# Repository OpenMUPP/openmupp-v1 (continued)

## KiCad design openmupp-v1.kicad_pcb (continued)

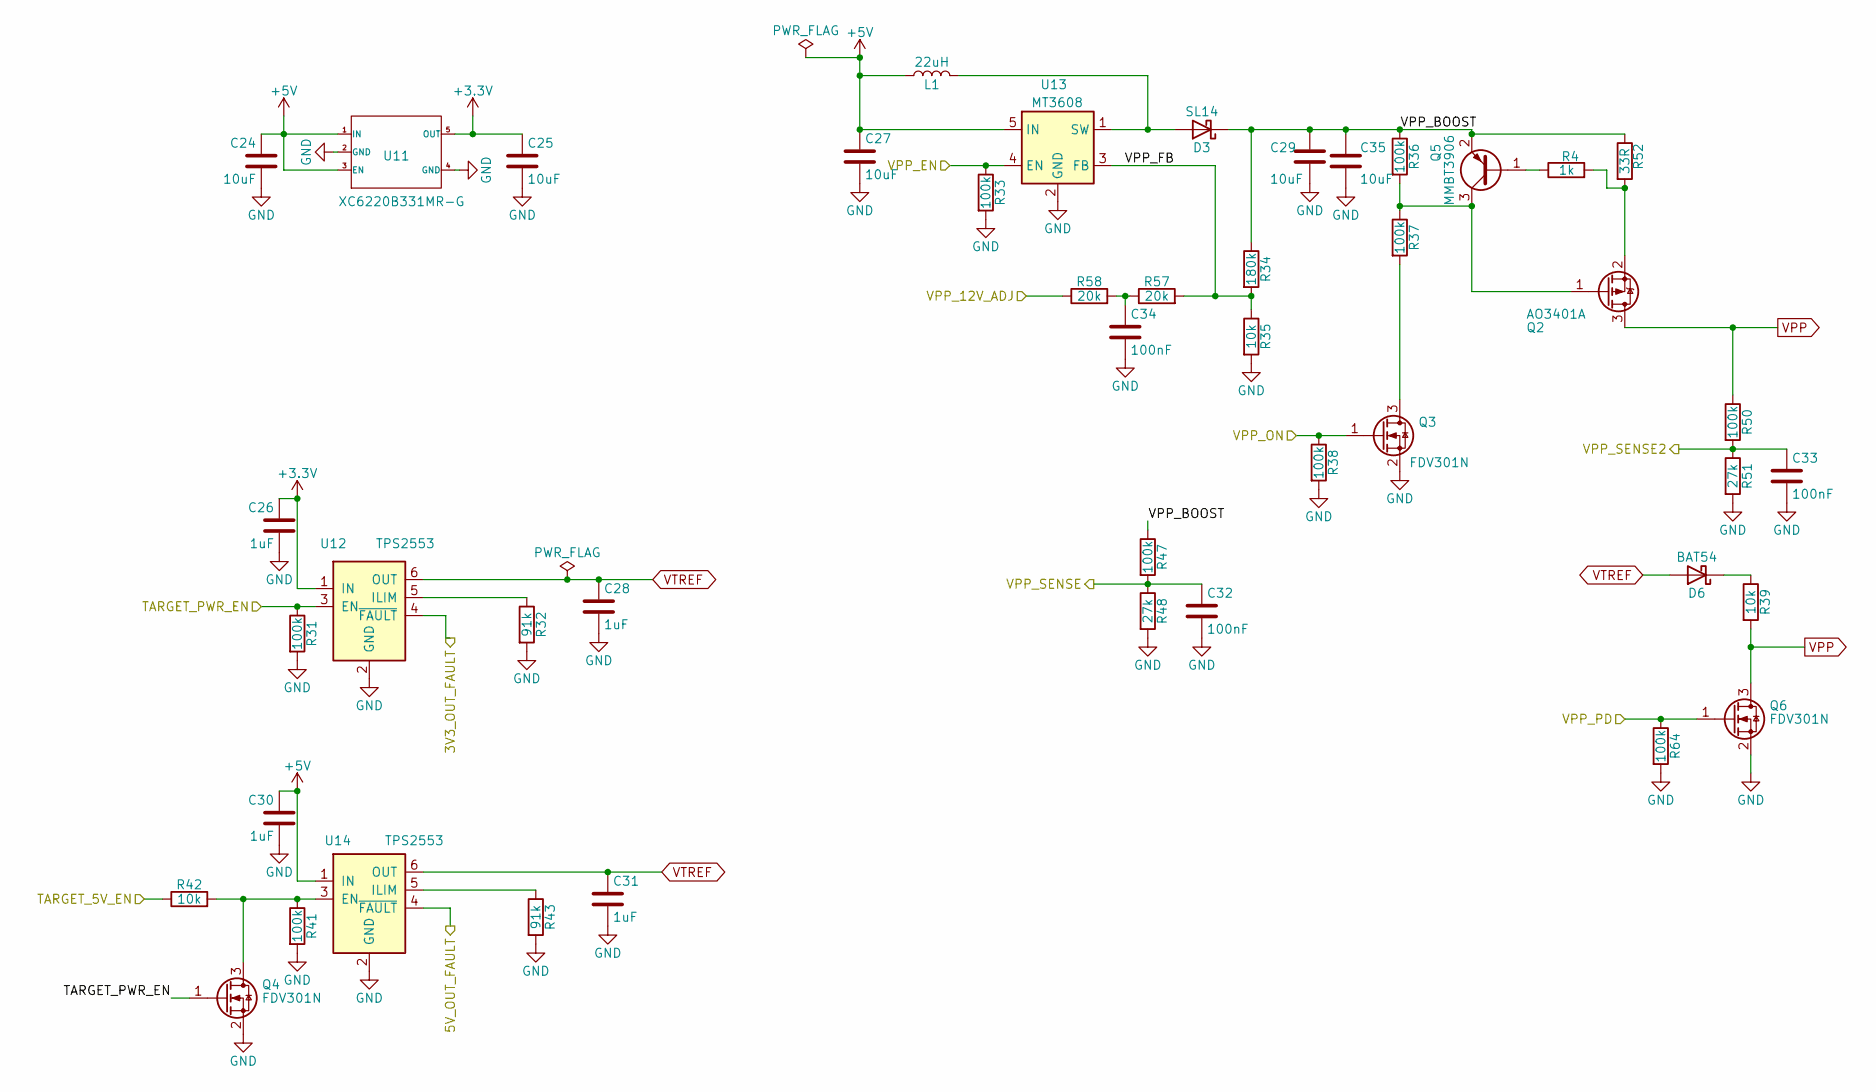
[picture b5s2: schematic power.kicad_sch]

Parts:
C24, C25: 10uF; C_1206; LCSC C13585
C26, C28, C30, C31: 1uF; C_0603; LCSC C15849
C27, C29, C35: 10uF; C_0805; LCSC C15850
C32, C33, C34: 100nF; C_0603; LCSC C14663
D3: SL14; D_SOD-123; LCSC C698818
D6: BAT54; D_SOD-323; LCSC C21107
L1: 22uH; L_FNR5040S; LCSC C167971
Q2: AO3401A; SOT-23; LCSC C15127
Q3, Q4, Q6: FDV301N; SOT-23; LCSC C15310
Q5: MMBT3906; SOT-23; LCSC C2940
R4: 1k; R_0402; LCSC C11702
R31, R33, R36, R37, R38, R41, R47, R50, R64: 100k; R_0402; LCSC C25741
R32, R43: 91k; R_0603; LCSC C23265
R34: 180k; R_0402; LCSC C25760
R35, R39, R42: 10k; R_0402; LCSC C25744
R48, R51: 27k; R_0402; LCSC C25771
R52: 33R; R_0402; LCSC C25105
R57, R58: 20k; R_0402; LCSC C25765
U11: XC6220B331MR-G; SOT23_5L; LCSC C3040644
U12, U14: TPS2553; SOT-23-6; LCSC C111738
U13: MT3608; SOT23_6L; LCSC C84817

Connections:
/3V3_OUT_FAULT: U12.4 (~FAULT); also elsewhere on the board
/5V_OUT_FAULT: U14.4 (~FAULT); also elsewhere on the board
/Power/VPP_BOOST: C29.1, C35.1, D3.1 (K), Q5.2 (E), R34.1, R36.1, R47.1, R52.1
/Power/VPP_FB: R34.2, R35.1, R57.2, U13.3 (FB)
/TARGET_5V_EN: R42.1; also elsewhere on the board
/TARGET_PWR_EN: Q4.1 (G), R31.1, U12.3 (EN); also elsewhere on the board
/VPP_12V_ADJ: R58.1; also elsewhere on the board
/VPP_EN: R33.1, U13.4 (EN); also elsewhere on the board
/VPP_ON: Q3.1 (G), R38.1; also elsewhere on the board
/VPP_PD: Q6.1 (G), R64.1; also elsewhere on the board
/VPP_SENSE: C32.1, R47.2, R48.1; also elsewhere on the board
/VPP_SENSE2: C33.1, R50.2, R51.1; also elsewhere on the board
unnamed: C34.1, R57.1, R58.2
unnamed: D3.2 (A), L1.2, U13.1 (SW)
unnamed: D6.1 (K), R39.1
unnamed: Q2.1 (G), Q5.3 (C), R36.2, R37.1
unnamed: Q2.2 (S), R4.2, R52.2
unnamed: Q3.3 (D), R37.2
unnamed: Q4.3 (D), R41.1, R42.2, U14.3 (EN)
unnamed: Q5.1 (B), R4.1
unnamed: R32.1, U12.5 (ILIM)
unnamed: R43.1, U14.5 (ILIM)
VPP: Q2.3 (D), Q6.3 (D), R39.2, R50.1; also elsewhere on the board

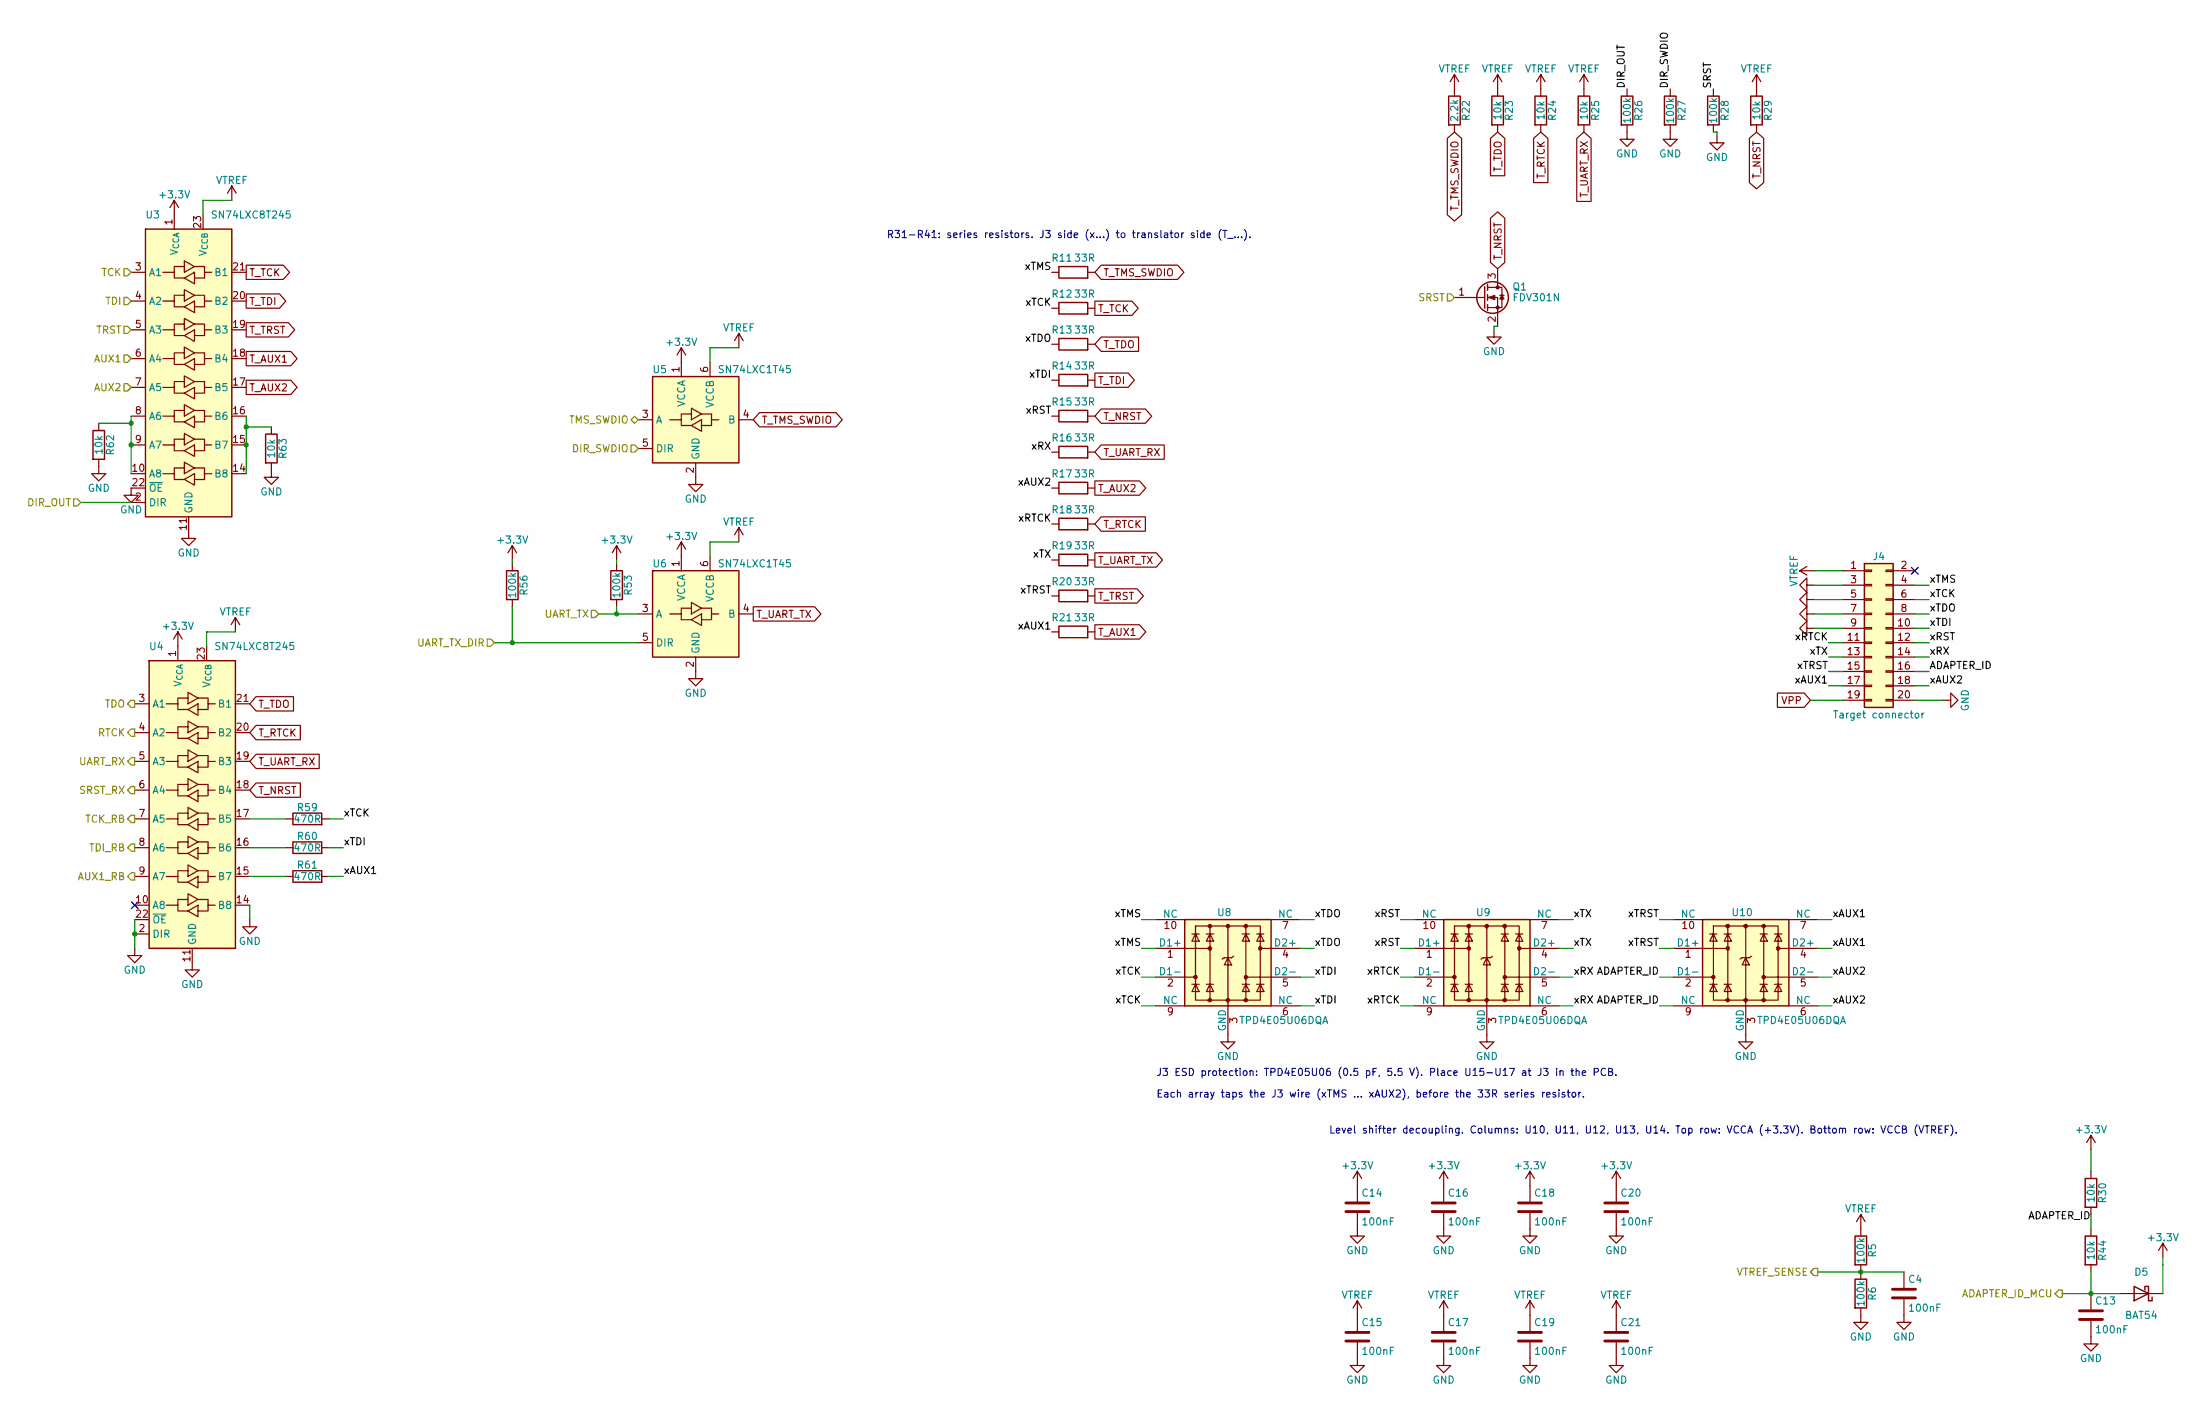
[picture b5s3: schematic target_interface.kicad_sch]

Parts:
C4, C13, C14, C15, C16, C17, C18, C19, C20, C21: 100nF; C_0603; LCSC C14663
D5: BAT54; D_SOD-323; LCSC C21107
J4: Target connector; IDC-Header_2x10_P2.54mm_Horizontal
Q1: FDV301N; SOT-23; LCSC C15310
R5, R6, R26, R27, R28, R53, R56: 100k; R_0402; LCSC C25741
R11, R12, R13, R14, R15, R16, R17, R18, R19, R20, R21: 33R; R_0402; LCSC C25105
R22: 2.2k; R_0402; LCSC C25879
R23, R24, R25, R29, R30, R44, R62, R63: 10k; R_0402; LCSC C25744
R59, R60, R61: 470R; R_0402; LCSC C25117
U3, U4: SN74LXC8T245; TSSOP-24_4.4x7.8mm_P0.65mm; LCSC C4363995
U5, U6: SN74LXC1T45; SOT-23-6; LCSC C4364198
U8, U9, U10: TPD4E05U06DQA; USON-10_2.5x1.0mm_P0.5mm; LCSC C138714

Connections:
/ADAPTER_ID_MCU: C13.1, D5.2 (A), R44.2; also elsewhere on the board
/AUX1: U3.6 (A4); also elsewhere on the board
/AUX1_RB: U4.9 (A7); also elsewhere on the board
/AUX2: U3.7 (A5); also elsewhere on the board
/DIR_OUT: R26.1, U3.2 (DIR); also elsewhere on the board
/DIR_SWDIO: R27.1, U5.5 (DIR); also elsewhere on the board
/RTCK: U4.4 (A2); also elsewhere on the board
/SRST: Q1.1 (G), R28.1; also elsewhere on the board
/SRST_RX: U4.6 (A4); also elsewhere on the board
/TCK: U3.3 (A1); also elsewhere on the board
/TCK_RB: U4.7 (A5); also elsewhere on the board
/TDI: U3.4 (A2); also elsewhere on the board
/TDI_RB: U4.8 (A6); also elsewhere on the board
/TDO: U4.3 (A1); also elsewhere on the board
/TMS_SWDIO: U5.3 (A); also elsewhere on the board
/TRST: U3.5 (A3); also elsewhere on the board
/Target interface/ADAPTER_ID: J4.16, R30.2, R44.1, U10.2 (D1-), U10.9 (NC)
/Target interface/xAUX1: J4.17, R21.1, R61.2, U10.4 (D2+), U10.7 (NC)
/Target interface/xAUX2: J4.18, R17.1, U10.5 (D2-), U10.6 (NC)
/Target interface/xRST: J4.12, R15.1, U9.1 (D1+), U9.10 (NC)
/Target interface/xRTCK: J4.11, R18.1, U9.2 (D1-), U9.9 (NC)
/Target interface/xRX: J4.14, R16.1, U9.5 (D2-), U9.6 (NC)
/Target interface/xTCK: J4.6, R12.1, R59.2, U8.2 (D1-), U8.9 (NC)
/Target interface/xTDI: J4.10, R14.1, R60.2, U8.5 (D2-), U8.6 (NC)
/Target interface/xTDO: J4.8, R13.1, U8.4 (D2+), U8.7 (NC)
/Target interface/xTMS: J4.4, R11.1, U8.1 (D1+), U8.10 (NC)
/Target interface/xTRST: J4.15, R20.1, U10.1 (D1+), U10.10 (NC)
/Target interface/xTX: J4.13, R19.1, U9.4 (D2+), U9.7 (NC)
/UART_RX: U4.5 (A3); also elsewhere on the board
/UART_TX: R53.2, U6.3 (A); also elsewhere on the board
/UART_TX_DIR: R56.2, U6.5 (DIR); also elsewhere on the board
/VTREF_SENSE: C4.1, R5.2, R6.1; also elsewhere on the board
unnamed: R62.1, U3.8 (A6), U3.9 (A7), U3.10 (A8)
unnamed: R63.1, U3.14 (B8), U3.15 (B7), U3.16 (B6)
unnamed: R59.1, U4.17 (B5)
unnamed: R60.1, U4.16 (B6)
unnamed: R61.1, U4.15 (B7)
T_AUX1: R21.2, U3.18 (B4)
T_AUX2: R17.2, U3.17 (B5)
T_NRST: Q1.3 (D), R15.2, R29.2, U4.18 (B4)
T_RTCK: R18.2, R24.2, U4.20 (B2)
T_TCK: R12.2, U3.21 (B1)
T_TDI: R14.2, U3.20 (B2)
T_TDO: R13.2, R23.2, U4.21 (B1)
T_TMS_SWDIO: R11.2, R22.2, U5.4 (B)
T_TRST: R20.2, U3.19 (B3)
T_UART_RX: R16.2, R25.2, U4.19 (B3)
T_UART_TX: R19.2, U6.4 (B)
VPP: J4.19; also elsewhere on the board

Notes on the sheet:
J3 ESD protection: TPD4E05U06 (0.5 pF, 5.5 V). Place U15-U17 at J3 in the PCB.
Each array taps the J3 wire (xTMS ... xAUX2), before the 33R series resistor.
R31-R41: series resistors. J3 side (x...) to translator side (T_...).
Level shifter decoupling. Columns: U10, U11, U12, U13, U14. Top row: VCCA (+3.3V). Bottom row: VCCB (VTREF).

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
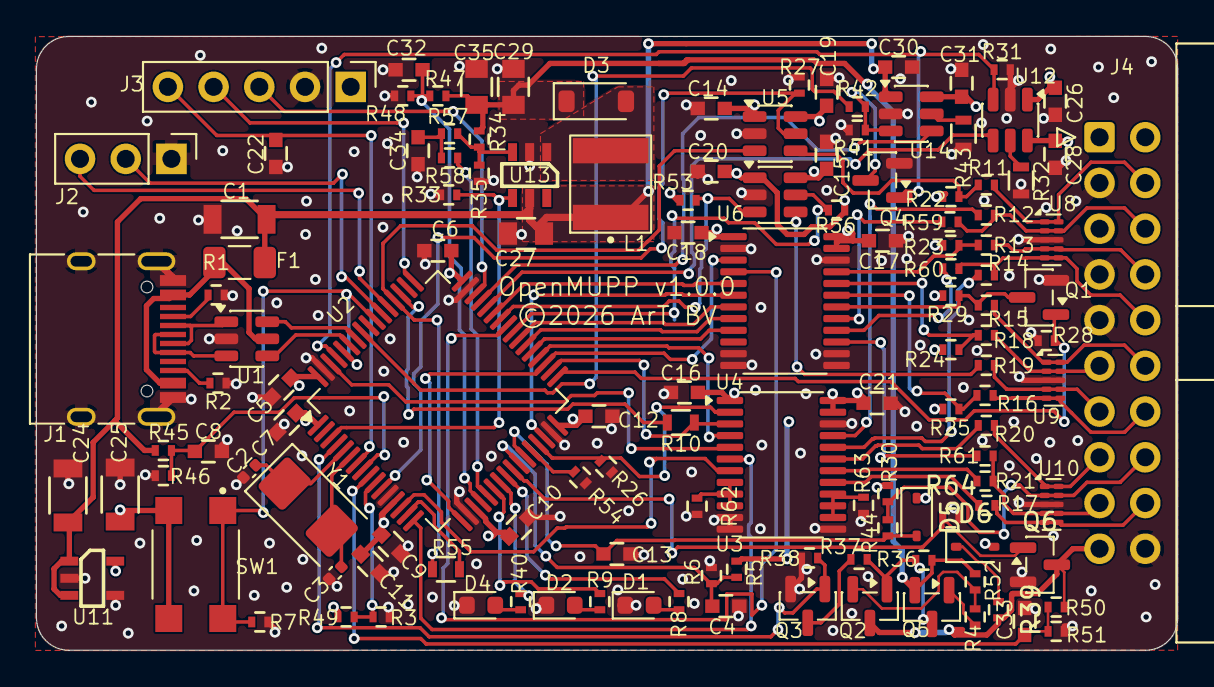
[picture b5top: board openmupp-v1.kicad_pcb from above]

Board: 4 copper layers, 63.4 x 34.1 mm, 131 parts (0 on the bottom side), 101 nets.

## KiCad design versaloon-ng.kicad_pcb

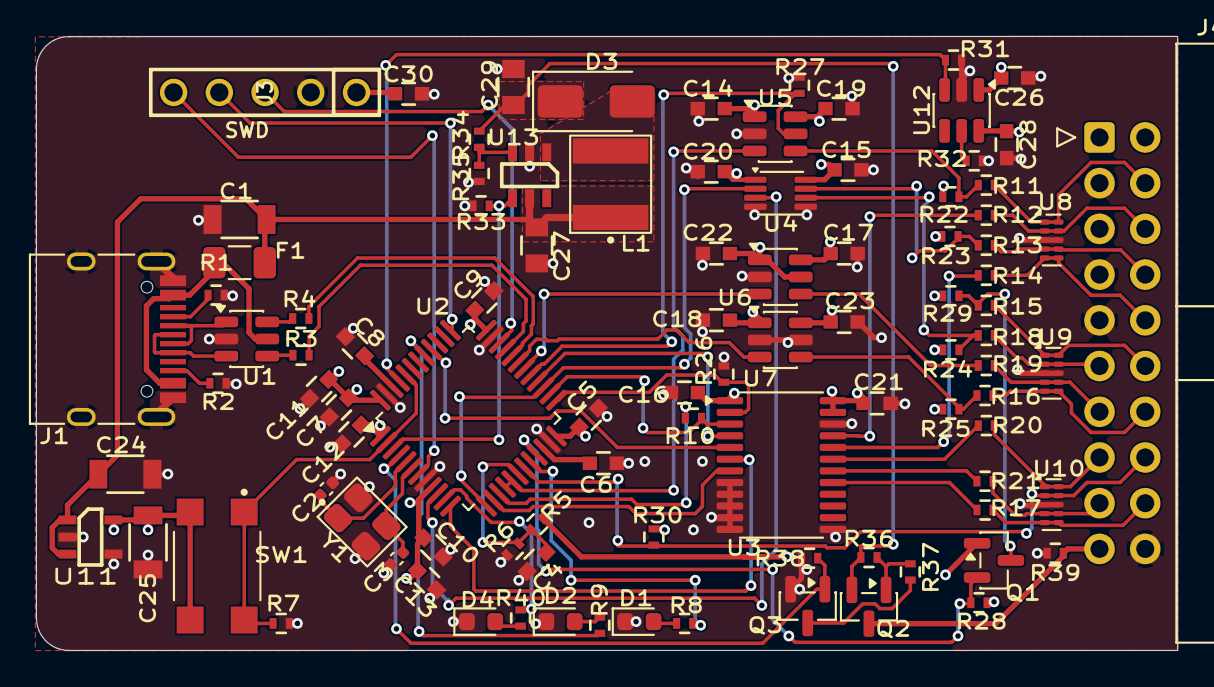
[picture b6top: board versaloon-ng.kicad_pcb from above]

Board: 4 copper layers, 63.4 x 34.1 mm, 97 parts (0 on the bottom side), 75 nets.

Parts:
C1, C24, C25: 10uF; C_1206
C2, C3: 5.6pF; C_0402_1005Metric
C4, C5, C7, C9, C10, C12, C14, C15, C16, C17, C18, C19, C20, C21, C22, C23, C30: 100nF; C_0603
C6, C8: 2.2uF; C_0603
C11: 4.7uF; C_0603
C13, C26, C28: 1uF; C_0603
C27, C29: 10uF; C_0805
D1, D4: LED state; LED_0603_1608Metric
D2: LED USB; LED_0603_1608Metric
D3: SL14; D_SMA
F1: 750mA; Fuse_1206_3216Metric
J1: USB_C_Receptacle_USB2.0_16P; USB_C_Receptacle_HRO_TYPE-C-31-M-12
J3: SWD; CON_HDR_1x5_2.54mm
J4: Target connector; IDC-Header_2x10_P2.54mm_Horizontal
L1: 22uH; L_FNR5040S
Q1, Q3: BSS138; SOT-23
Q2: AO3401A; SOT-23
R1, R2: 5K1; R_0402
R3, R4: 22R; R_0402
R5, R6, R26, R27, R31, R33, R36, R38, R39: 100k; R_0402
R7, R22, R23, R24, R25, R28, R29, R30, R35, R37: 10k; R_0402
R8, R9, R40: 1k; R_0402
R10: 0R; R_0402
R11, R12, R13, R14, R15, R16, R17, R18, R19, R20, R21: 33R; R_0402
R32: 51k; R_0402
R34: 191k; R_0402
SW1: BOOT0; SW_Push_HanElectricity_TS1109_4.5x4.5mm_H3.8mm
U1: USBLC6-2SC6; SOT-23-6
U2: STM32H523CCTx; LQFP-48_7x7mm_P0.5mm
U3: SN74LXC8T245; TSSOP-24_4.4x7.8mm_P0.65mm
U4: SN74LXC2T45; VSSOP-8_2.3x2mm_P0.5mm
U5, U6, U7: SN74LXC1T45; SOT-23-6
U8, U9, U10: TPD4E05U06DQA; USON-10_2.5x1.0mm_P0.5mm
U11: XC6220B331MR-G; SOT23_5L
U12: TPS2553; SOT-23-6
U13: MT3608; SOT23_6L
Y1: 24MHz; Crystal_SMD_NDK_NX3225GA_3.2x2.5mm

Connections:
+3.3V: C5.1, C7.1, C9.1, C10.1, C11.1, C12.1, C13.1, C14.1, C16.1, C18.1, C20.1, C22.1, C25.1, C26.1, C30.1, J3.1, Q1.1 (G), R28.1, R30.1, SW1.2, U2.1 (VBAT), U2.9 (VDDA), U2.24 (VDD), U2.36 (VDD), U2.48 (VDD), U3.1 (V_{CCA}), U4.1 (VCCA), U5.1 (VCCA), U6.1 (VCCA), U6.5 (DIR), U7.1 (VCCA), U11.5 (OUT), U12.1 (IN)
+5V: C1.1, C24.1, C27.1, F1.1, L1.1, U11.1 (IN), U11.3 (EN), U13.5 (IN)
/ADAPTER_ID: J4.16, R30.2, U2.19 (PB1), U10.2 (D1-), U10.9 (NC)
/AUX1: U2.12 (PA2), U3.6 (A4)
/AUX2: U2.14 (PA4), U3.7 (A5)
/BOOT0: R7.1, SW1.1, U2.2 (PC13), U2.44 (BOOT0)
/DIR_OUT: R26.1, U2.25 (PB12), U3.2 (DIR)
/DIR_SWDIO: R27.1, U2.29 (PA8), U5.5 (DIR)
/HSE_IN: C2.1, U2.5 (PH0), Y1.1
/HSE_OUT: C3.1, U2.6 (PH1), Y1.3
/LED_STATE1: R8.1, U2.20 (PB2)
/LED_STATE2: R40.1, U2.11 (PA1)
/LED_USB: R9.1, U2.41 (PB5)
/RTCK: U2.10 (PA0), U4.3 (A2)
/SRST: Q1.2 (S), R28.2, U2.21 (PB10)
/TARGET_PWR_EN: R31.1, U2.45 (PB8), U12.3 (EN)
/TCK: R10.2, U2.26 (PB13), U3.3 (A1)
/TDI: U2.28 (PB15), U3.4 (A2)
/TDO: U2.13 (PA3), U2.27 (PB14), U4.2 (A1)
/TMS_SWDIO: U2.16 (PA6), U2.17 (PA7), U5.3 (A)
/TRST: U2.40 (PB4(NJTRST)), U3.5 (A3)
/Target interface/xAUX1: J4.17, R21.1, U10.4 (D2+), U10.7 (NC)
/Target interface/xAUX2: J4.18, R17.1, U10.5 (D2-), U10.6 (NC)
/Target interface/xRST: J4.12, R15.1, U9.1 (D1+), U9.10 (NC)
/Target interface/xRTCK: J4.11, R18.1, U9.2 (D1-), U9.9 (NC)
/Target interface/xRX: J4.14, R16.1, U9.5 (D2-), U9.6 (NC)
/Target interface/xTCK: J4.6, R12.1, U8.2 (D1-), U8.9 (NC)
/Target interface/xTDI: J4.10, R14.1, U8.5 (D2-), U8.6 (NC)
/Target interface/xTDO: J4.8, R13.1, U8.4 (D2+), U8.7 (NC)
/Target interface/xTMS: J4.4, R11.1, U8.1 (D1+), U8.10 (NC)
/Target interface/xTRST: J4.15, R20.1, U10.1 (D1+), U10.10 (NC)
/Target interface/xTX: J4.13, R19.1, U9.4 (D2+), U9.7 (NC)
/UART_RX: U2.31 (PA10), U7.3 (A)
/UART_TX: U2.30 (PA9), U6.3 (A)
/VPP_EN: R33.1, U2.3 (PC14), U13.4 (EN)
/VPP_ON: Q3.1 (G), R38.1, U2.4 (PC15)
/VTREF_SENSE: C4.1, R5.2, R6.1, U2.18 (PB0)
GND: C1.2, C2.2, C3.2, C4.2, C5.2, C6.2, C7.2, C8.2, C9.2, C10.2, C11.2, C12.2, C13.2, C14.2, C15.2, C16.2, C17.2, C18.2, C19.2, C20.2, C21.2, C22.2, C23.2, C24.2, C25.2, C26.2, C27.2, C28.2, C29.2, C30.2, D1.1 (K), D2.1 (K), D4.1 (K), J1.A1 (GND), J1.A12 (GND), J1.B1 (GND), J1.B12 (GND), J1.S1 (SHIELD), J3.2, J4.3, J4.5, J4.7, J4.9, J4.20, Q3.2 (S), R1.2, R2.1, R6.2, R7.2, R26.2, R27.2, R31.2, R32.2, R33.2, R35.2, R38.2, R39.2, U1.2 (GND), U2.8 (VSSA), U2.23 (VSS), U2.35 (VSS), U2.47 (VSS), U3.8 (A6), U3.9 (A7), U3.10 (A8), U3.11 (GND), U3.12 (GND), U3.13 (GND), U3.22 (~OE), U4.4 (GND), U4.5 (DIR), U5.2 (GND), U6.2 (GND), U7.2 (GND), U7.5 (DIR), U8.3 (GND), U8.8 (GND), U9.3 (GND), U9.8 (GND), U10.3 (GND), U10.8 (GND), U11.2 (GND), U11.4 (GND), U12.2 (GND), U13.2 (GND), Y1.2 (G), Y1.4 (G)
unnamed: C6.1, U2.22 (VCAP)
unnamed: C8.1, U2.46 (VCAP)
unnamed: D1.2 (A), R8.2
unnamed: D2.2 (A), R9.2
unnamed: D3.2 (A), L1.2, U13.1 (SW)
unnamed: C29.1, D3.1 (K), Q2.2 (S), R34.1, R36.1
unnamed: D4.2 (A), R40.2
unnamed: J1.A5 (CC1), R1.1
unnamed: J1.B5 (CC2), R2.2
unnamed: J1.A6 (D+), J1.B6 (D+), U1.3 (I/O2)
unnamed: J1.A7 (D-), J1.B7 (D-), U1.1 (I/O1)
unnamed: Q2.1 (G), R36.2, R37.1
unnamed: Q3.3 (D), R37.2
unnamed: R3.1, U1.4 (I/O2)
unnamed: R4.1, U1.6 (I/O1)
unnamed: R10.1, U2.15 (PA5)
unnamed: R32.1, U12.5 (ILIM)
unnamed: R34.2, R35.1, U13.3 (FB)
RESET: J3.5, U2.7 (NRST)
SWDCLK: J3.4, U2.37 (PA14(JTCK)
SWDIO: J3.3, U2.34 (PA13(JTMS)
T_AUX1: R21.2, U3.18 (B4)
T_AUX2: R17.2, U3.17 (B5)
T_NRST: Q1.3 (D), R15.2, R29.2
T_RTCK: R18.2, R24.2, U4.6 (B2)
T_TCK: R12.2, U3.21 (B1)
T_TDI: R14.2, U3.20 (B2)
T_TDO: R13.2, R23.2, U4.7 (B1)
T_TMS_SWDIO: R11.2, R22.2, U5.4 (B)
T_TRST: R20.2, U3.19 (B3)
T_UART_RX: R16.2, R25.2, U7.4 (B)
T_UART_TX: R19.2, U6.4 (B)
USB_D+: R3.2, U2.33 (PA12)
USB_D-: R4.2, U2.32 (PA11)
VBUS: F1.2, J1.A4 (VBUS), J1.A9 (VBUS), J1.B4 (VBUS), J1.B9 (VBUS), U1.5 (VBUS)
VPP: J4.19, Q2.3 (D), R39.1
VTREF: C15.1, C17.1, C19.1, C21.1, C23.1, C28.1, J4.1, R5.1, R22.1, R23.1, R24.1, R25.1, R29.1, U3.23 (V_{CCB}), U3.24 (V_{CCB}), U4.8 (VCCB), U5.6 (VCCB), U6.6 (VCCB), U7.6 (VCCB), U12.6 (OUT)
